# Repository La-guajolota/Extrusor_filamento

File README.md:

<!-- @format -->

# ⚙️ Extrusora de Filamento para Impresión 3D

Este proyecto ofrece un diseño abierto para **reciclar** y **reutilizar** residuos plásticos (PLA, ABS, PETG…) convirtiéndolos en filamento de 1.75 mm de alta calidad, fomentando la sostenibilidad en impresión 3D.

---

## 📑 Contenidos

1. [Descripción General](#descripción-general)
2. [Características Principales](#características-principales)
3. [Flujo de Trabajo](#flujo-de-trabajo)
4. [Retos Técnicos](#retos-técnicos)
5. [Estructura del Repositorio](#estructura-del-repositorio)
6. [Requisitos y Dependencias](#requisitos-y-dependencias)
7. [Instalación y Uso](#instalación-y-uso)
8. [Colaboradores](#colaboradores)
9. [Licencia](#licencia)

---

## Descripción General

La **Extrusora de Filamento** procesa:

- **Reciclaje** de piezas fallidas y sobrantes de PLA, ABS, PETG…
- **Triturado** y filtrado de partículas a tamaño óptimo.
- **Fusión** controlada con termopares K y MAX6675.
- **Extrusión** de filamento de 1.75 mm con control de diámetro en tiempo real.
- **Enbobinado** sincronizado con motores NEMA para tensión constante.

Diseño modular y open-source para que cualquier persona pueda reproducirlo y mejorarlo.

---

## ✨ Características Principales

- **Modularidad**: subsistemas mecánico, electrónico y firmware independientes.
- **Control térmico**: 3 termopares + resistencias de abrazadera.
- **Motores sincronizados**: extrusión vs. bobinado para diámetro estable.
- **Interfaz de usuario**: LCD + encoder rotativo con menú configurables.
- **Documentación completa**: CAD, esquemas, lista de materiales y guía paso a paso.

---

## 🔄 Flujo de Trabajo

1. **Recolección y clasificación**

   - Separar por tipo de plástico (PLA, ABS, PETG…)
   - Eliminar adhesivos, polvo y contaminantes

2. **Triturado**

   - Triturar al tamaño adecuado
   - Filtrar fragmentos excesivamente grandes

3. **Fusión y extrusión**

   - Alimentar extrusor
   - Aplicar temperatura y presión
   - Control de diámetro en tiempo real

4. **Enfriamiento**

   - Baño o flujo de aire
   - Tensión constante para evitar deformaciones

5. **Embobinado y almacenamiento**
   - Medir diámetro final
   - Enrollar con tensión controlada
   - Etiquetar y almacenar

---

## 🎯 Retos Técnicos

1. **Triturado**

   - Potencia y geometría de cuchillas adecuadas
   - Filtrado de partículas homogéneas

2. **Extrusión**

   - Temperaturas variables según material
   - Presión y velocidad constantes para diámetro uniforme

3. **Enfriamiento**

   - Evitar fragilidad por enfriado demasiado rápido

4. **Embobinado**
   - Sistema guiado para prevenir enredos
   - Monitoreo de diámetro durante el bobinado

---

## 📂 Estructura del Repositorio

```text
.
├── Electrónica/               # Esquemas, PCB y conexiones
├── Mecánica/                  # Modelos CAD y planos
├── Firmware/                  # Código STM32CubeIDE
├── Investigación_fuentes/     # Artículos y referencias
├── Presupuestos_materiales/   # Lista de componentes y costes
├── LICENSE                    # Licencia MIT
└── README.md                  # Documentación principal
```

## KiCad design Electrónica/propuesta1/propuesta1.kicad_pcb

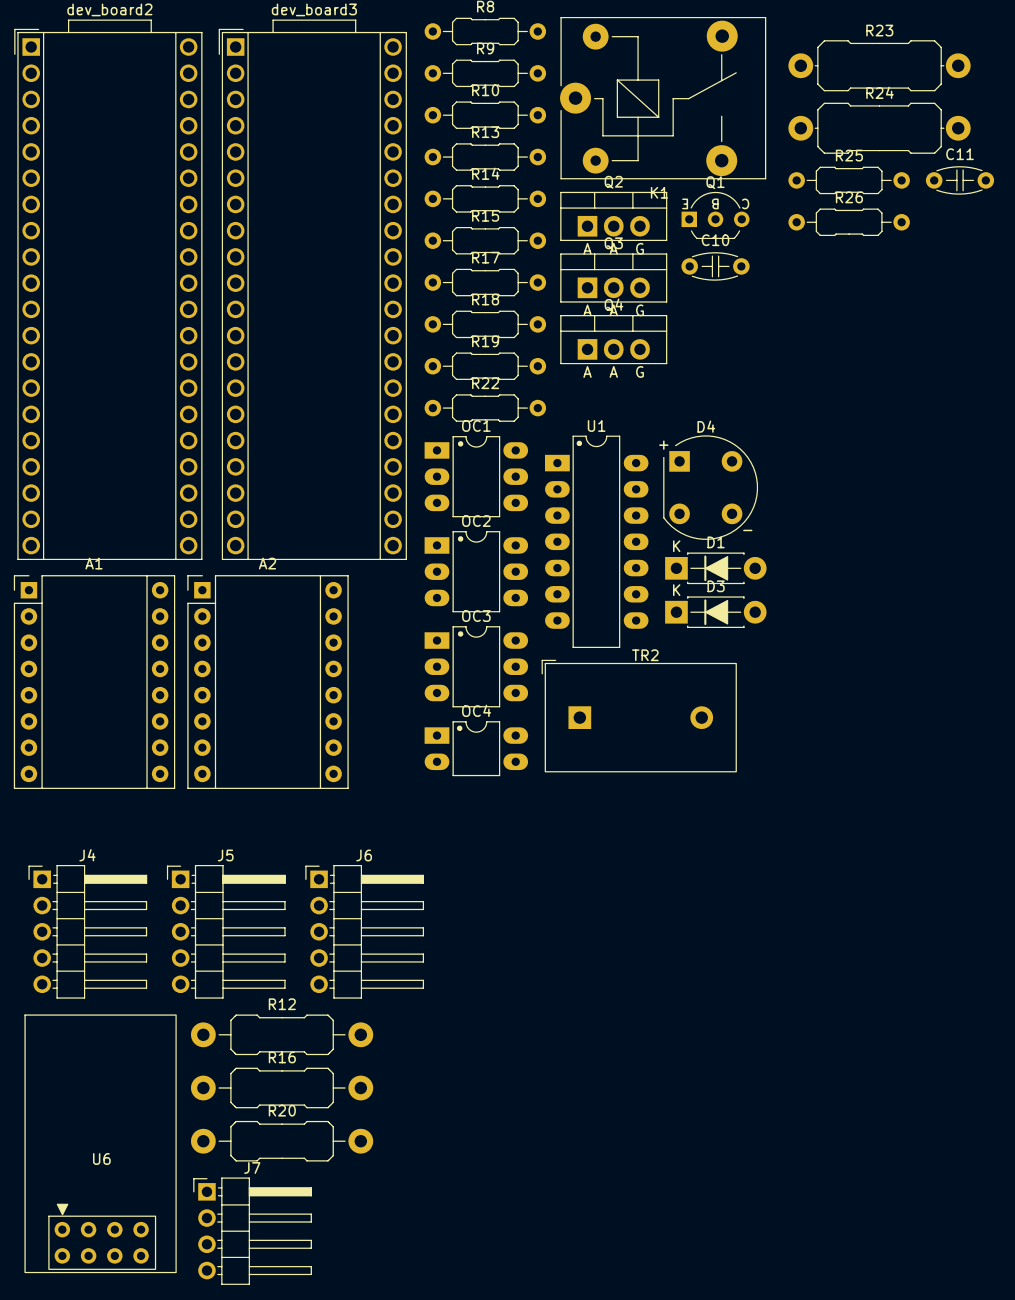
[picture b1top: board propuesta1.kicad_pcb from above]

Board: 2 copper layers, 42 parts (0 on the bottom side), 39 nets, no tracks yet.

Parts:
A1, A2: Pololu_Breakout_A4988; Pololu_Breakout-16_15.2x20.3mm
C10, C11: 100nf; C_Disc_D4.7mm_W2.5mm_P5.00mm
D1: 1N4003; D_DO-41_SOD81_P7.62mm_Horizontal
D3: 1N4001; D_DO-41_SOD81_P7.62mm_Horizontal
D4: 2W10G; Diode_Bridge_Round_D9.8mm
J4, J5, J6: Max6675_modulo; PinHeader_1x05_P2.54mm_Horizontal
J7: ESP01; PinHeader_1x04_P2.54mm_Horizontal
K1: SANYOU_SRD_Form_C; Relay_SPDT_SANYOU_SRD_Series_Form_C
OC1, OC2, OC3: MOC3021M; DIP-6_W7.62mm_LongPads
OC4: PC817; DIP-4_W7.62mm_LongPads
Q1: 2N2222A-TO92; TO-92_Inline_Wide_EBC
Q2, Q3, Q4: BTA12-600B; TO-220-3_Vertical_AAG
R8, R9, R13, R14, R17, R18: 180; R_Axial_DIN0207_L6.3mm_D2.5mm_P10.16mm_Horizontal
R10, R15, R19: 1.2K; R_Axial_DIN0207_L6.3mm_D2.5mm_P10.16mm_Horizontal
R12, R16, R20: 39 1W; R_Axial_DIN0411_L9.9mm_D3.6mm_P15.24mm_Horizontal
R22: 10k; R_Axial_DIN0207_L6.3mm_D2.5mm_P10.16mm_Horizontal
R23, R24: 5K 2W; R_Axial_DIN0414_L11.9mm_D4.5mm_P15.24mm_Horizontal
R25: 1k; R_Axial_DIN0207_L6.3mm_D2.5mm_P10.16mm_Horizontal
R26: 2k; R_Axial_DIN0207_L6.3mm_D2.5mm_P10.16mm_Horizontal
TR2: ZMCT103C; Transformer_Zeming_ZMCT103C
U1: TL084CN; DIP-14_W7.62mm_LongPads
U6: ESP-01S; ESP-01
dev_board2, dev_board3: Black_pill_stm32f411; Electrosmith_Daisy_Seed

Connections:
5VCC: A1.2 (VDD), A2.2 (VDD), C10.2, C11.2, R22.1, dev_board2.40 (5V), dev_board3.40 (5V)
12VCC_nema: A1.8 (VMOT), A2.8 (VMOT)
127VAC: K1.1, R24.1
+3.3V: J7.1, U6.7 (VCC)
+5V: J4.2, J5.2, J6.2
+12VA: D3.1 (K), K1.5, U1.4 (V+)
/Rx_mcu_esp01: J7.2, U6.1 (TX)
/Tx_mcu_esp01: J7.3, U6.8 (RX)
/cs: J4.4, J5.4, J6.4
/sck: J4.3, J5.3, J6.3
/so: J4.5, J5.5, J6.5
/zc: R25.2, R26.1
GND: J4.1, J5.1, J6.1, J7.4, U6.2 (GND)
GND1: Q1.1 (E), TR2.1, U1.11 (V-)
GND2: A1.1 (GND), A2.1 (GND), C10.1, C11.1, OC1.2, OC2.2, OC3.2, OC4.3, R26.2, dev_board2.19 (G), dev_board2.39 (G), dev_board3.19 (G), dev_board3.39 (G)
GND_nema: A1.7 (GND), A2.7 (GND)
NEUT: D1.1 (K), Q2.1 (A1), Q3.1 (A1), Q4.1 (A1), R23.1
unnamed: R9.1, R10.2
unnamed: R14.1, R15.2
unnamed: R18.1, R19.2
unnamed: D3.2 (A), K1.2, Q1.3 (C)
unnamed: D4.2 (1), R23.2
unnamed: D4.4 (2), R24.2
unnamed: D4.1 (+), OC4.1
unnamed: D4.3 (-), OC4.2
unnamed: OC1.1, R8.1
unnamed: OC1.6, R9.2
unnamed: OC2.1, R13.1
unnamed: OC2.6, R14.2
unnamed: OC3.1, R17.1
unnamed: OC3.6, R18.2
unnamed: OC4.4, R22.2
unnamed: Q2.2 (A2), R10.1, R12.1
unnamed: OC1.4, Q2.3 (G)
unnamed: Q3.2 (A2), R15.1, R16.1
unnamed: OC2.4, Q3.3 (G)
unnamed: Q4.2 (A2), R19.1, R20.1
unnamed: OC3.4, Q4.3 (G)
unnamed: U1.1, U1.2 (-)

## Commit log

2025-03-10 Primera carga
2025-03-10 Primera carga readme
2025-03-10 actualización de readme
2025-03-11 new file: Presupuestos_materiales/README.md
2025-03-31 new file: .gitignore new file: "Electr\303\263nica/propuesta1/propuesta1-backups/propuesta1-2025-03-12_202321.zip" new file: "Electr\303\263nica/propuesta1/propuesta1-backups/propuesta1-2025-03-19_20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
2025-03-31 Actualización de elementos de la rama
2025-03-31 deleted: Presupuestos_materiales/compras/.~lock.ODC_ELE001.xlsx# deleted: Presupuestos_materiales/compras/ODC_ELE001.xlsx
2025-04-02 modified: pcb
2025-04-02 deleted: Presupuestos_materiales/compras/Unit.xlsx
2025-04-02 new file: Firmware/.metadata/.ide.log new file: Firmware/.metadata/.lock new file: Firmware/.metadata/.log new file: Firmware/.metadata/.log4j2.xml new file: Firmware/.metadata/.plugins/com.st.stm32c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
2025-04-03 new file: "Electr\303\263nica/propuesta1/propuesta1-backups/propuesta1-2025-04-02_221845.zip" new file: "Electr\303\263nica/propuesta1/propuesta1-backups/propuesta1-2025-04-02_222917.zip" new file: "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
2025-04-06 modified: .gitignore
2025-04-24 modified: pid_lib max6675_lib AS5048B_lib extrusor_process_lib
2025-04-24 nuevo README.md y organización de carpetas
2025-04-24 modified: README.md
2025-04-24 resolucion de conflicto merge
2025-04-24 new file: README.md
2025-04-25 Liscencia agregada
2025-04-25 Actualización firmware
2025-04-27 Lectura de los max6675 secuencialmente corregida
2025-05-01 Reorganización y actualización de la carpeta de Investigación_funtes
2025-05-01 Actualización de driver para los encoders AS5048B
2025-05-01 Modificación: driver AS5048B |
2025-05-01 Actualización de firmware
2025-05-01 Reorganización de carpetas y añadido de información nueva
2025-05-01 Reorganización de archivos
2025-05-01 Limpieza de la rama
2025-05-15 Cascaded PID
2025-05-15 kikcad
2025-05-15 Peletizer_controller first commit
